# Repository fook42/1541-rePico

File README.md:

# 1541-rePico
replacement of analog-part of Commodore 1541-Floppy devices based on Pi-Pico(2)

## preface/credits ##
this project was derived from the original 1541-rebuild from Thorsten Kattanek (https://github.com/ThKattanek/1541-rebuild) !
parts of his code were taken from there and adopted for Raspberry Pico and modified to handle disk images differently. Thanks!

the C64/C16 selector-programm was developed and implemented by [PeiselUlli](https://github.com/peiselulli69) !

thanks to [BensonRSI](https://github.com/BensonRSI) for adding debugging documentation, dev-containers and github-magic !

## Features ##

latest version:
- software: 1.7.3
- hardware: 1.7.0

### Hardware ###

single board, size 59mm x 60 mm

- Raspberry Pico2 socket/solder-pads
- VIA 40pin socket
- levelshifter (BSS138 & 74LVC4245) for stable signals
- connectors for
  - I2C Display
  - SPI SD-Card adapter
  - Rotary-Encoder + Switch (KY-040 compatible)
  - Write-Protect-Signal
  - passive Buzzer

one size fits for all 1541 models.

## how to build ##

-> [interactive BOM](/hardware/bom/ibom.html)

-> [step-by-step guide](/doc/HWSetup.md)

### Software ###

#### Pico2 Firmware ####

- mounting of D64 & G64 & PRG Files
- 35 & 42 track image files supported
- read and write access for both D64 & G64
- sd-card hotswap feature (refresh of directory content)

#### C64/C16/VC20 Image Selector ####

- browsing through sd-card content via "virtual disk-image"
  - subdirectory support
  - 4 way scrolling
  - usage of joystick for browsing possible
- highlighting and selecting of different file-types (D64,G64,PRG,Folder)
- shows TXT files onscreen
- simple mounting and also fastloading of selected entry
- supports C64-PAL, C64-NTSC, VC20 and C16 computers

## how to build ##

### prepare tools (linux) ###

```
sudo apt install cmake libusb-1.0-0-dev build-essential pkg-config python3 xxd gcc-arm-none-eabi libnewlib-arm-none-eabi libstdc++-arm-none-eabi-newlib acme
```

### pico-sdk ###

from : <https://github.com/raspberrypi/pico-sdk>

- clone this repo
- create a environment variable called "PICO_SDK_PATH" which points to this repo
- place a "export PICO_SDK_PATH= <path to your pico-sdk>" at the end of your .profile script
- then cd into this repo-folder and initialize the mbedtls submodule (picotool mentiones this)

all in one:
```
git clone https://github.com/raspberrypi/pico-sdk.git
export PICO_SDK_PATH=$(pwd)/pico-sdk
echo "export PICO_SDK_PATH=$PICO_SDK_PATH" >> ~/.profile"
cd pico-sdk
git submodule update --init lib/mbedtls
```

### picotool ###

from : <https://github.com/raspberrypi/picotool>

- clone this repo
- install the picotool as described in README.md and BUILDING.md file there

```
git clone https://github.com/raspberrypi/picotool.git
```

### build steps ###

make sure submodules are initialized and up-to-date (like NoOS-Fat-lib)

```
git submodule update --init
git pull --recurse-submodules
```

prepare build-folder / configure Ninja for build the cmake project

```
cd firmware
mkdir build
cd build
cmake .. -D BUILD_MENUPRG=OFF -D COMPRESS_MENUPRG=ON -D PCB_VERSION=17
```

optional cmake variables are:

| Variable | Values | Description |
| :--- | :---: | :--- |
| BUILD_MENUPRG | ON*/OFF | let ACME compile the provided menu.asm-code. Otherwise the shipped, precompiled "menu.prg" will be used. |
| BUILD_SELECTORPRG | ON*/OFF | let PETCAT convert the boot-selector basic code to PRG. Otherwise the shipped, precompiled "selector.prg" will be used. |
| COMPRESS_MENUPRG | ON*/OFF | uses dali binary compression to generate a smaller menu-prg object |
| PCB_VERSION | 0..17* | defines which PCB version is used -> enables specific code features according to pcb-layout (like sound output) |

(* is default)

now trigger a build

```
make -j
```

## howto flash ##

connect your pico2 via USB cable and use picotool to flash the firmware

```
picotool load -t uf2 1541-rePico.uf2 -x -f
```

## debugging with OpenOCD ##

### prerequisites ###

- **CMSIS-DAP Compatible Debugger** (e.g., Raspberry Pi Debug Probe, STLink, or SEGGER J-Link) 
get binaries for a pico here : https://github.com/raspberrypi/debugprobe
- **OpenOCD** installed ( built in devcontainer or  with "build_openocd.sh")
- **gdb-multiarch** for GDB debugging ( preinstalled in devcontainer )

### setup ###

1. Connect your debugger to the Pico using the SWD pins:
   - SWCLK → GPIO 24 (or pin 20)
   - SWDIO → GPIO 25 (or pin 21)
   - GND → GND

2. Ensure the debugger is connected via USB to your development machine

### starting OpenOCD ###

Start OpenOCD in a terminal:

```
openocd -f interface/cmsis-dap.cfg -f target/rp2350.cfg
```

OpenOCD will listen on port 3333 for GDB connections.

### debugging in VS Code ###

VS Code launch configurations are available:

**Pico Debug (Cortex-Debug)** - Integrated debugging with OpenOCD

#### using Cortex-Debug (recommended) ####

Press `F5` or select "Pico Debug (Cortex-Debug)" from the Run menu. This will:
- Start OpenOCD automatically
- Load your firmware
- Break at `main()`
- Allow step debugging, breakpoints, and variable inspection

#### using external OpenOCD ####

1. Start OpenOCD in a terminal (see above)
2. Select "Pico Debug (Cortex-Debug with external OpenOCD)" from Run menu
3. VS Code will connect to the running OpenOCD instance

### useful GDB commands ###

When debugging, common GDB commands include:

```
continue         # Resume execution
step             # Step into function
next             # Step over function
break <func>     # Set breakpoint at function
break <file>:<line>  # Set breakpoint at file:line
print <var>      # Print variable value
display <var>    # Show variable on each step
backtrace        # Show call stack
```

### troubleshooting ###

**"Device not found"**: 
- Check CMSIS-DAP debugger is connected
- Verify SWD pin connections
- Try `openocd -d` for debug output
- Connect the USB for the targetdevice, then the USB for debugprobe
( to keep correct order of /dev/ttyACMx )

**GDB connection failed**: 
- Ensure OpenOCD is running on port 3333
- Check firewall settings

# documentation #

## project documentation ##

t.b.d.

## supported disk formats ##

currently [D64](/doc/D64.TXT) and [G64](/doc/G64.TXT) are supported as for reading and writing.  
as bonus, **PRG** files can be loaded by an on-the-fly routine that creates a valid D64 image out of it.

additionaly a small tool [conv_x64](/tools) is provided that allows easy conversion from one to the other on you linux-pc.

## Pictures ##

impressions of current setup and PCB can be found [here](/doc/pictures).

## Links ##

- great collection of basics about disk-image-formats can be found here:  
<https://ist.uwaterloo.ca/~schepers/formats.html>

- forum64 project discussion thread (base of 1541-rebuild and 1541-rePico)  
<https://www.forum64.de/index.php?thread/59884-laufwerk-der-1541-emulieren>

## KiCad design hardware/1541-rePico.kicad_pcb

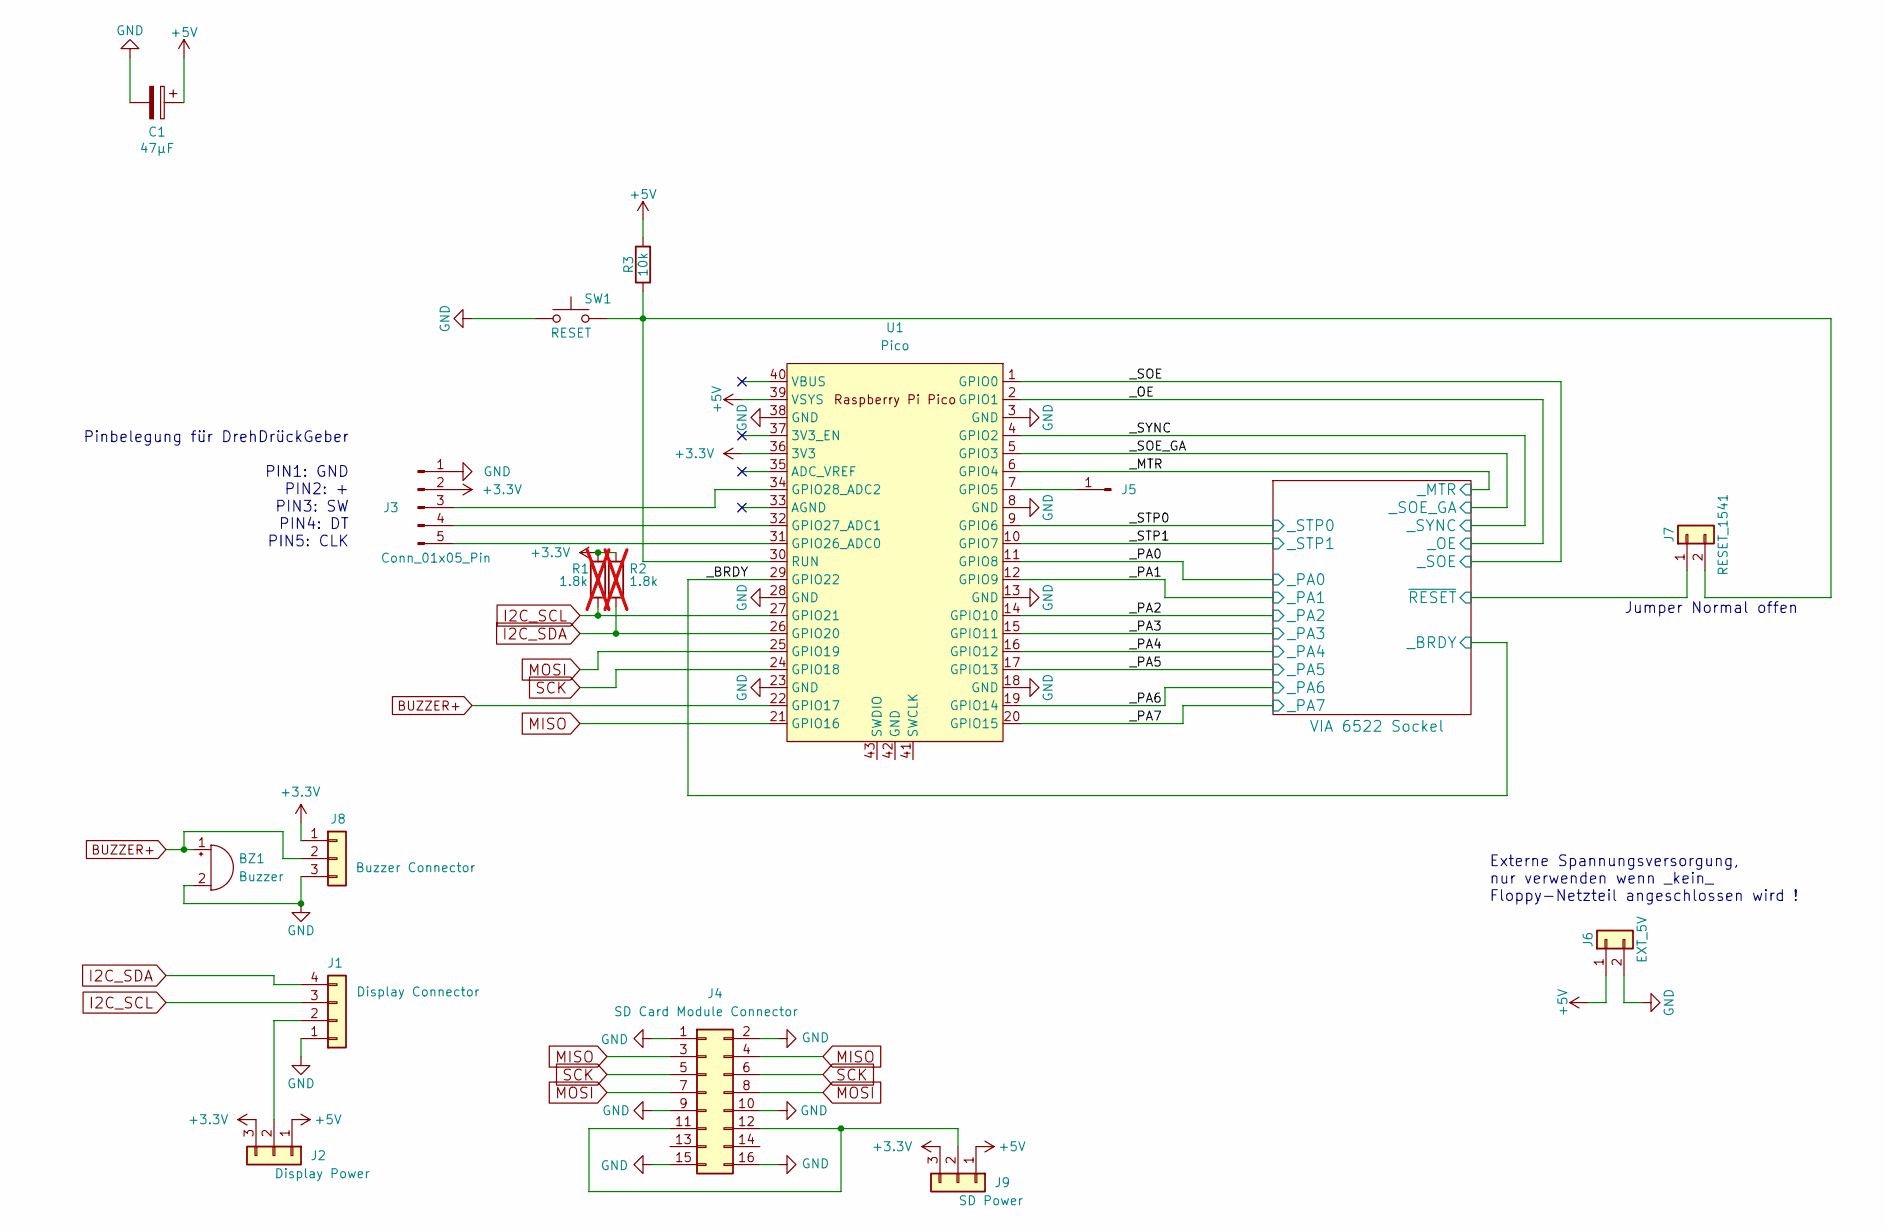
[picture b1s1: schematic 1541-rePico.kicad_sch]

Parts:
BZ1: Buzzer; MagneticBuzzer_StarMicronics_QMX
C1: 47µF; CP_Radial_D5.0mm_P2.50mm
J1: Display Connector; PinSocket_1x04_P2.54mm_Vertical
J2: Display Power; PinHeader_1x03_P2.54mm_Vertical
J3: Conn_01x05_Pin; PinHeader_1x05_P2.54mm_Vertical
J4: SD Card Module Connector; PinSocket_2x08_P2.54mm_Vertical
J5: Conn_01x01_Pin; PinHeader_1x01_P2.54mm_Vertical
J6: EXT_5V; PinHeader_1x02_P2.54mm_Vertical
J7: RESET_1541; PinHeader_1x02_P2.54mm_Vertical
J8: Buzzer Connector; PinHeader_1x03_P2.54mm_Vertical
J9: SD Power; PinHeader_1x03_P2.54mm_Vertical
R1, R2: 1.8k; R_0805_2012Metric; not fitted
R3: 10k; R_Axial_DIN0207_L6.3mm_D2.5mm_P10.16mm_Horizontal
SW1: RESET; SW_PUSH_6mm_H5mm
U1: Pico; RPi_Pico_SMD_TH

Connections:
+3.3V: J2.3, J3.2, J8.1, J9.3, R1.1, R2.1, U1.36 (3V3); also elsewhere on the board
+5V: C1.1, J2.1, J6.1, J9.1, R3.2, U1.39 (VSYS); also elsewhere on the board
/VIA 6522 Sockel/~RESET: J7.1; also elsewhere on the board
/_BRDY: U1.29 (GPIO22); also elsewhere on the board
/_MTR: U1.6 (GPIO4); also elsewhere on the board
/_OE: U1.2 (GPIO1); also elsewhere on the board
/_PA0: U1.11 (GPIO8); also elsewhere on the board
/_PA1: U1.12 (GPIO9); also elsewhere on the board
/_PA2: U1.14 (GPIO10); also elsewhere on the board
/_PA3: U1.15 (GPIO11); also elsewhere on the board
/_PA4: U1.16 (GPIO12); also elsewhere on the board
/_PA5: U1.17 (GPIO13); also elsewhere on the board
/_PA6: U1.19 (GPIO14); also elsewhere on the board
/_PA7: U1.20 (GPIO15); also elsewhere on the board
/_SOE: U1.1 (GPIO0); also elsewhere on the board
/_SOE_GA: U1.5 (GPIO3); also elsewhere on the board
/_STP0: U1.9 (GPIO6); also elsewhere on the board
/_STP1: U1.10 (GPIO7); also elsewhere on the board
/_SYNC: U1.4 (GPIO2); also elsewhere on the board
BUZZER+: BZ1.1 (+), J8.2, U1.22 (GPIO17)
GND: BZ1.2 (-), C1.2, J1.1, J3.1, J4.1, J4.2, J4.9, J4.10, J4.15, J4.16, J6.2, J8.3, SW1.1, U1.3 (GND), U1.8 (GND), U1.13 (GND), U1.18 (GND), U1.23 (GND), U1.28 (GND), U1.38 (GND); also elsewhere on the board
I2C_SCL: J1.3, R1.2, U1.27 (GPIO21)
I2C_SDA: J1.4, R2.2, U1.26 (GPIO20)
MISO: J4.3, J4.4, U1.21 (GPIO16)
MOSI: J4.7, J4.8, U1.25 (GPIO19)
unnamed: J1.2, J2.2
unnamed: J3.3, U1.34 (GPIO28_ADC2)
unnamed: J3.4, U1.32 (GPIO27_ADC1)
unnamed: J3.5, U1.31 (GPIO26_ADC0)
unnamed: J4.11, J4.12, J9.2
unnamed: J5.1, U1.7 (GPIO5)
unnamed: J7.2, R3.1, SW1.2, U1.30 (RUN)
SCK: J4.5, J4.6, U1.24 (GPIO18)

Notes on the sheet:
Jumper Normal offen
Externe Spannungsversorgung, nur verwenden wenn _kein_ Floppy-Netzteil angeschlossen wird !
Pinbelegung für DrehDrückGeber PIN1: GND PIN2: + PIN3: SW PIN4: DT PIN5: CLK

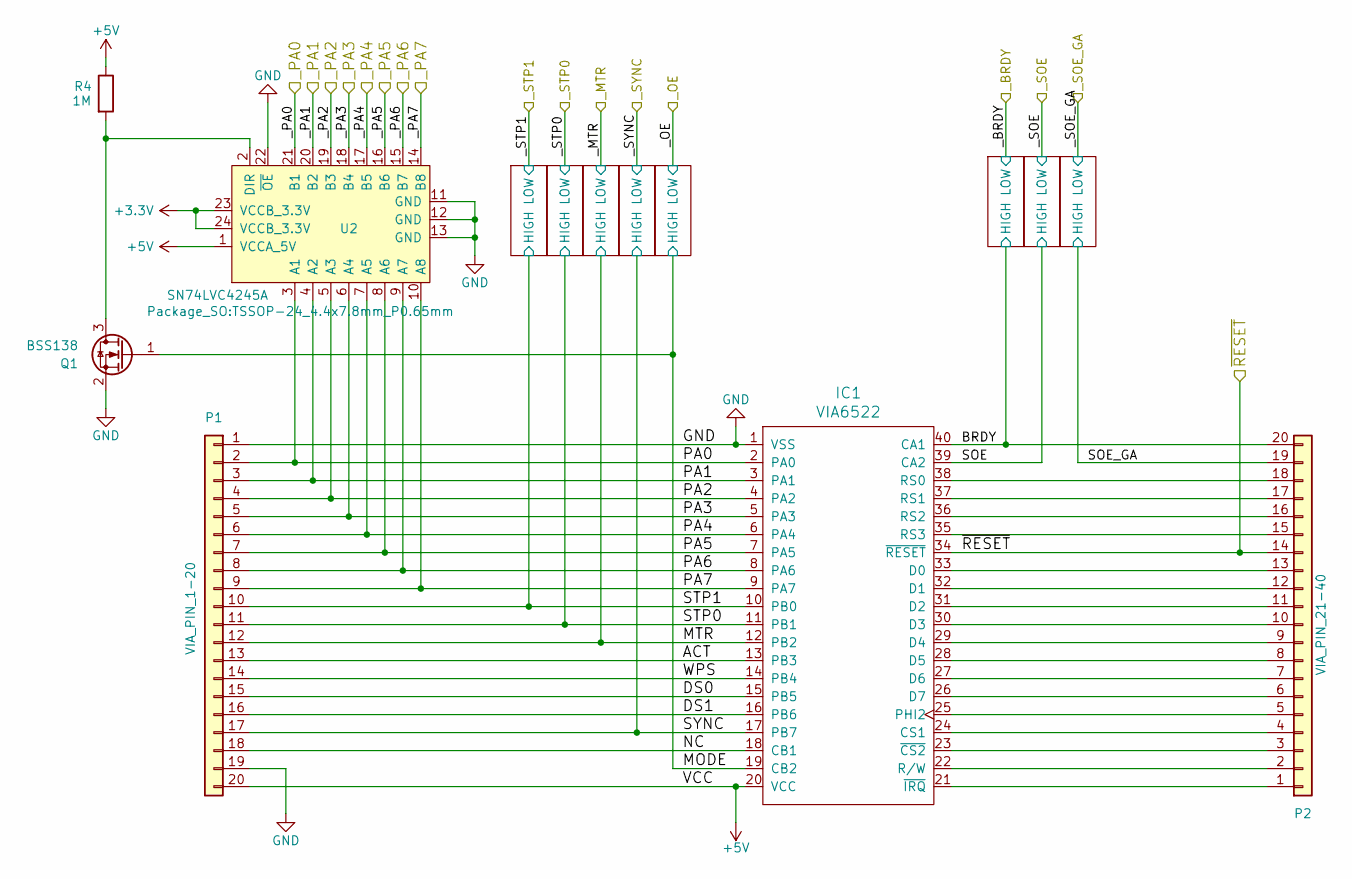
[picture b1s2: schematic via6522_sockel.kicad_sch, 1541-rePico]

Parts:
IC1: VIA6522; DIP-40_W15.24mm_Socket_LongPads
P1: VIA_PIN_1-20; PinHeader_1x20_P2.54mm_Vertical
P2: VIA_PIN_21-40; PinHeader_1x20_P2.54mm_Vertical
Q1: BSS138; SOT-23
R4: 1M; R_0603_1608Metric
U2: SN74LVC4245A; TSSOP-24_4.4x7.8mm_P0.65mm

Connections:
+3.3V: U2.23 (VCCB_3.3V), U2.24 (VCCB_3.3V); also elsewhere on the board
+5V: IC1.20 (VCC), P1.20, R4.1, U2.1 (VCCA_5V); also elsewhere on the board
/VIA 6522 Sockel/ACT: IC1.13 (PB3), P1.13
/VIA 6522 Sockel/BRDY: IC1.40 (CA1), P2.20; also elsewhere on the board
/VIA 6522 Sockel/DS0: IC1.15 (PB5), P1.15
/VIA 6522 Sockel/DS1: IC1.16 (PB6), P1.16
/VIA 6522 Sockel/MODE: IC1.19 (CB2), Q1.1 (G); also elsewhere on the board
/VIA 6522 Sockel/MTR: IC1.12 (PB2), P1.12; also elsewhere on the board
/VIA 6522 Sockel/NC: IC1.18 (CB1), P1.18
/VIA 6522 Sockel/PA0: IC1.2 (PA0), P1.2, U2.3 (A1)
/VIA 6522 Sockel/PA1: IC1.3 (PA1), P1.3, U2.4 (A2)
/VIA 6522 Sockel/PA2: IC1.4 (PA2), P1.4, U2.5 (A3)
/VIA 6522 Sockel/PA3: IC1.5 (PA3), P1.5, U2.6 (A4)
/VIA 6522 Sockel/PA4: IC1.6 (PA4), P1.6, U2.7 (A5)
/VIA 6522 Sockel/PA5: IC1.7 (PA5), P1.7, U2.8 (A6)
/VIA 6522 Sockel/PA6: IC1.8 (PA6), P1.8, U2.9 (A7)
/VIA 6522 Sockel/PA7: IC1.9 (PA7), P1.9, U2.10 (A8)
/VIA 6522 Sockel/SOE: IC1.39 (CA2); also elsewhere on the board
/VIA 6522 Sockel/SOE_GA: P2.19; also elsewhere on the board
/VIA 6522 Sockel/STP0: IC1.11 (PB1), P1.11; also elsewhere on the board
/VIA 6522 Sockel/STP1: IC1.10 (PB0), P1.10; also elsewhere on the board
/VIA 6522 Sockel/SYNC: IC1.17 (PB7), P1.17; also elsewhere on the board
/VIA 6522 Sockel/WPS: IC1.14 (PB4), P1.14
/VIA 6522 Sockel/~RESET: IC1.34 (~RESET), P2.14; also elsewhere on the board
/_PA0: U2.21 (B1); also elsewhere on the board
/_PA1: U2.20 (B2); also elsewhere on the board
/_PA2: U2.19 (B3); also elsewhere on the board
/_PA3: U2.18 (B4); also elsewhere on the board
/_PA4: U2.17 (B5); also elsewhere on the board
/_PA5: U2.16 (B6); also elsewhere on the board
/_PA6: U2.15 (B7); also elsewhere on the board
/_PA7: U2.14 (B8); also elsewhere on the board
GND: IC1.1 (VSS), P1.1, P1.19, Q1.2 (S), U2.11 (GND), U2.12 (GND), U2.13 (GND), U2.22 (~OE); also elsewhere on the board
unnamed: IC1.24 (CS1), P2.4
unnamed: IC1.33 (D0), P2.13
unnamed: IC1.32 (D1), P2.12
unnamed: IC1.31 (D2), P2.11
unnamed: IC1.30 (D3), P2.10
unnamed: IC1.29 (D4), P2.9
unnamed: IC1.28 (D5), P2.8
unnamed: IC1.27 (D6), P2.7
unnamed: IC1.26 (D7), P2.6
unnamed: IC1.25 (PHI2), P2.5
unnamed: IC1.38 (RS0), P2.18
unnamed: IC1.37 (RS1), P2.17
unnamed: IC1.36 (RS2), P2.16
unnamed: IC1.35 (RS3), P2.15
unnamed: IC1.22 (R/W), P2.2
unnamed: IC1.23 (~CS2), P2.3
unnamed: IC1.21 (~IRQ), P2.1
unnamed: Q1.3 (D), R4.2, U2.2 (DIR)

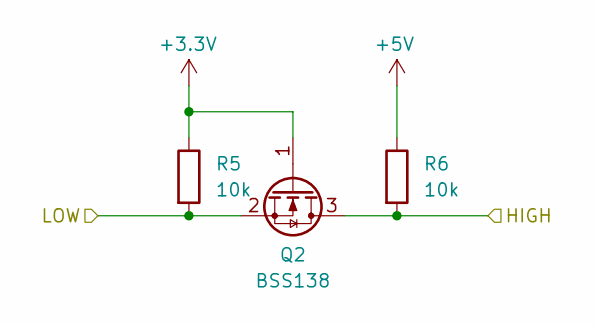
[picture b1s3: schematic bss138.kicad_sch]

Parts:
Q2: BSS138; SOT-23
R5, R6: 10k; R_0603_1608Metric

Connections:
+3.3V: Q2.1 (G), R5.1; also elsewhere on the board
+5V: R6.1; also elsewhere on the board
/VIA 6522 Sockel/STP1: Q2.3 (D), R6.2; also elsewhere on the board
/_STP1: Q2.2 (S), R5.2; also elsewhere on the board

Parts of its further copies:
Q3, Q4, Q5, Q6, Q7, Q8, Q9: BSS138; SOT-23
R7, R8, R9, R10, R11, R12, R13, R14, R15, R16, R17, R18, R19, R20: 10k; R_0603_1608Metric

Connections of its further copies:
+3.3V: Q3.1 (G), Q4.1 (G), Q5.1 (G), Q6.1 (G), Q7.1 (G), Q8.1 (G), Q9.1 (G), R7.1, R9.1, R11.1, R13.1, R15.1, R17.1, R19.1; also elsewhere on the board
+5V: R8.1, R10.1, R12.1, R14.1, R16.1, R18.1, R20.1; also elsewhere on the board
/VIA 6522 Sockel/BRDY: Q7.3 (D), R16.2; also elsewhere on the board
/VIA 6522 Sockel/MODE: Q6.3 (D), R14.2; also elsewhere on the board
/VIA 6522 Sockel/MTR: Q4.3 (D), R10.2; also elsewhere on the board
/VIA 6522 Sockel/SOE: Q8.3 (D), R18.2; also elsewhere on the board
/VIA 6522 Sockel/SOE_GA: Q9.3 (D), R20.2; also elsewhere on the board
/VIA 6522 Sockel/STP0: Q3.3 (D), R8.2; also elsewhere on the board
/VIA 6522 Sockel/SYNC: Q5.3 (D), R12.2; also elsewhere on the board
/_BRDY: Q7.2 (S), R15.2; also elsewhere on the board
/_MTR: Q4.2 (S), R9.2; also elsewhere on the board
/_OE: Q6.2 (S), R13.2; also elsewhere on the board
/_SOE: Q8.2 (S), R17.2; also elsewhere on the board
/_SOE_GA: Q9.2 (S), R19.2; also elsewhere on the board
/_STP0: Q3.2 (S), R7.2; also elsewhere on the board
/_SYNC: Q5.2 (S), R11.2; also elsewhere on the board

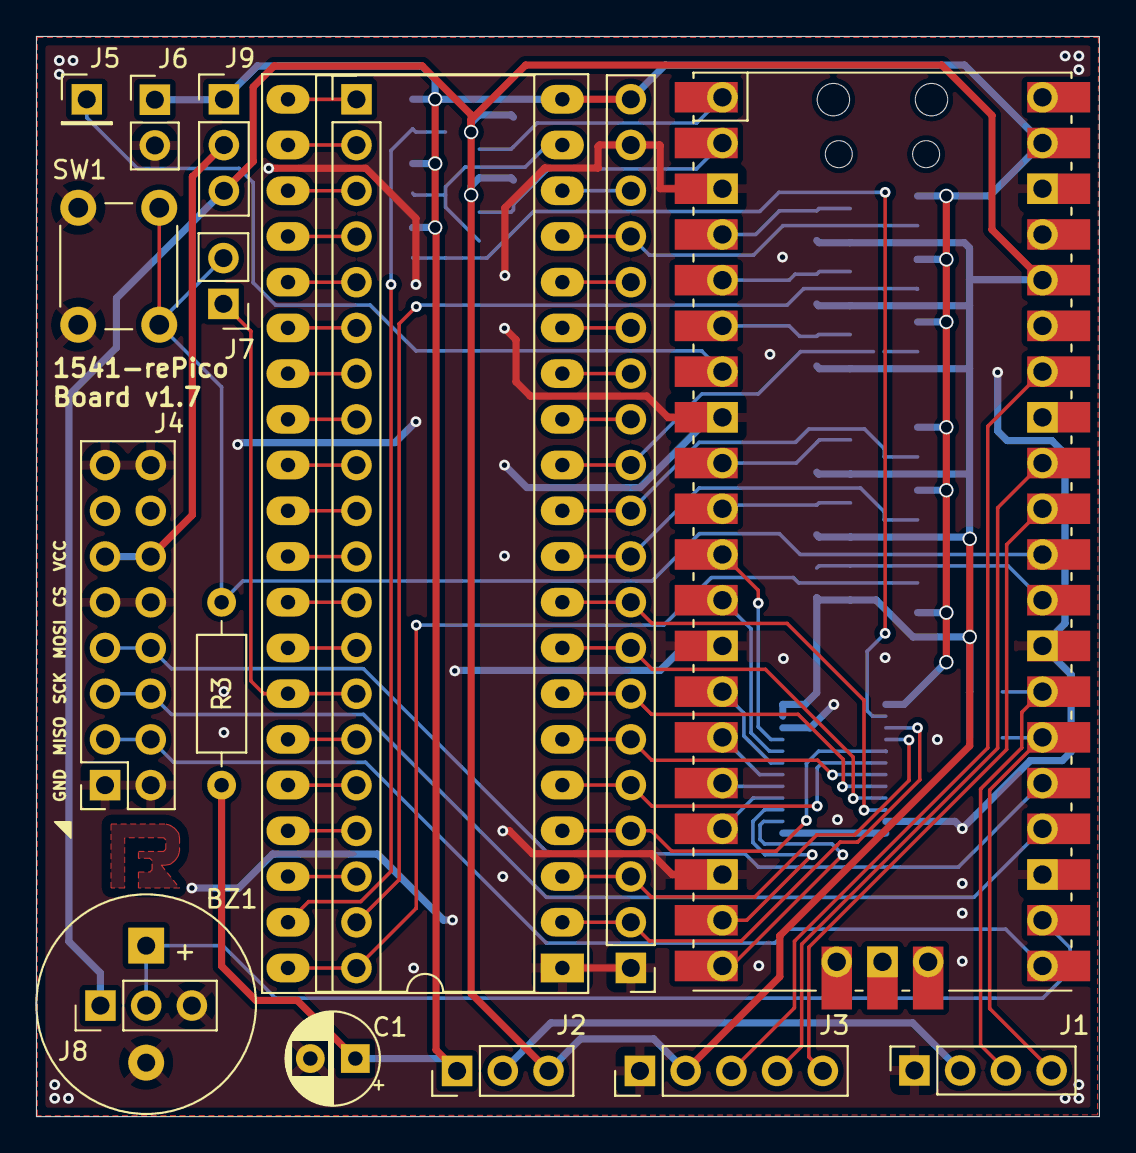
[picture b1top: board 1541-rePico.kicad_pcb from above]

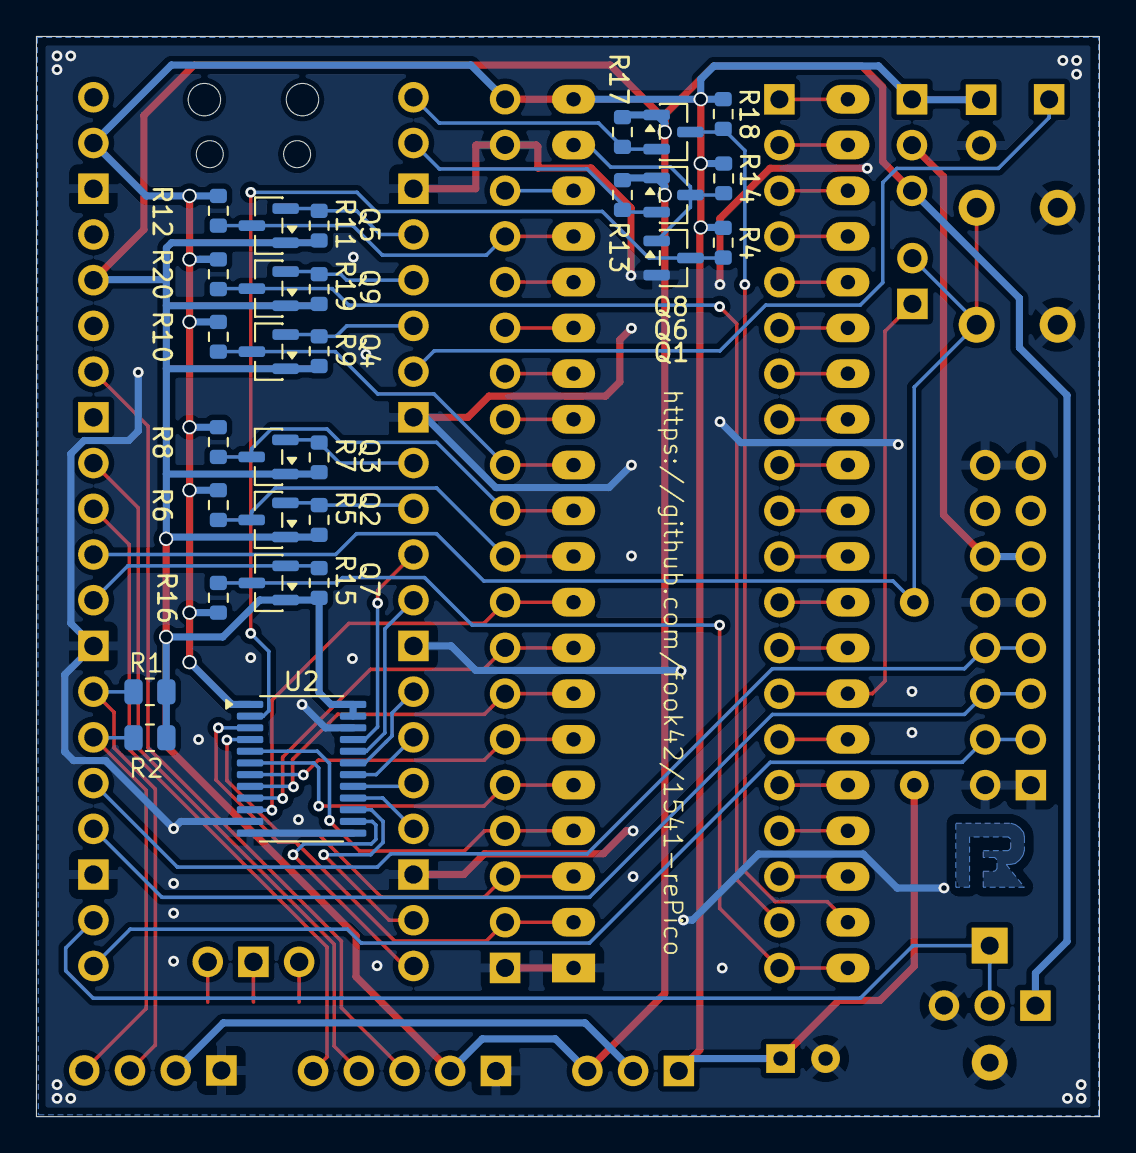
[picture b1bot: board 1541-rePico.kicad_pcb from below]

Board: 2 copper layers, 59.1 x 60.0 mm, 46 parts (29 on the bottom side), 72 nets.

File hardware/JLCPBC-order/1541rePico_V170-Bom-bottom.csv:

"Comment","Designator","Footprint","JLCPCB Part #"
"1M","R4","Resistor_SMD:R_0603_1608Metric","C22935"
"SN74LVC4245A","U2","Package_SO:TSSOP-24_4.4x7.8mm_P0.65mm","C7859"
"BSS138","Q1,Q2,Q3,Q4,Q5,Q6,Q7,Q8,Q9","Package_TO_SOT_SMD:SOT-23","C7420339"
"10k","R5,R6,R7,R8,R9,R10,R11,R12,R13,R14,R15,R16,R17,R18,R19,R20","Resistor_SMD:R_0603_1608Metric","C25804"

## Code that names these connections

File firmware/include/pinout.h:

/**********************************
 * header - pinout assignment for Pico2 to baseboard
 *
 * Author: F00K42
 * Last change: 2026/07/24
***********************************/

#include "hardware/spi.h"

// Via connection
#define GPIO_SOE    0
#define GPIO_OE     1
#define GPIO_SYNC   2
#define GPIO_SOE_GA 3
#define GPIO_MTR    4
#define GPIO_WPS    5
#define GPIO_STP0   6
#define GPIO_STP1   7

#define GPIO_PAPORT 8  //defines the first bit of 8
#define PAPORT_MASK (uint32_t)(0xFF<<GPIO_PAPORT)
/*
#define GPIO_PA0    8
#define GPIO_PA1    9
#define GPIO_PA2    10
#define GPIO_PA3    11
#define GPIO_PA4    12
#define GPIO_PA5    13
#define GPIO_PA6    14
#define GPIO_PA7    15
*/

// SPI defines
#define SPI_PORT    spi0
#define SPI_MISO    16
#define SPI_SCK     18
#define SPI_MOSI    19

// I2C defines
#define I2C_PORT    i2c0
#define I2C_SDA     20
#define I2C_SCL     21

// 3 für den Drück-Dreh-Schalter
#define GPIO_BT1    27
#define GPIO_BT2    26
#define GPIO_BT3    28

#define GPIO_BRDY   22

#define NOT_CONNECTED (-1)


#if PCB_VERSION>=17
#define GPIO_SND    17
#define SPI_CS      NOT_CONNECTED
#else
#define GPIO_SND    NOT_CONNECTED
#define SPI_CS      17
#endif

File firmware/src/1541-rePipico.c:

#include <stdio.h>
#include "pico/stdlib.h"
// #include "hardware/spi.h"
#include "hardware/i2c.h"
// #include "hardware/dma.h"
// #include "hardware/pio.h"
// #include "hardware/interp.h"
#include "hardware/timer.h"
#include "hardware/clocks.h"

#include "pinout.h"

#define _EXTERN_

#include "display.h"
#include "lcd.h"
#include "oled.h"
#include "i2c.h"
#include "gcr.h"
#include "menu.h"

#include "hw_config.h"
#include "f_util.h"
#include "ff.h"

uint8_t stepper_signal_puffer[0x80]; // Ringpuffer für Stepper Signale (128 Bytes)
volatile uint8_t stepper_signal_r_pos = 0;
volatile uint8_t stepper_signal_w_pos = 0;
volatile uint8_t stepper_signal_time = 0;
volatile uint8_t stepper_signal = 0;

// -- MENU preparation --
MENU_STRUCT main_menu;
MENU_STRUCT image_menu;
MENU_STRUCT settings_menu;
MENU_STRUCT info_menu;

enum  MENU_IDS{M_BACK, M_IMAGE, M_SETTINGS, M_INFO, \
               M_BACK_IMAGE, M_INSERT_IMAGE, M_UNMOUNT_IMAGE, M_WP_IMAGE, M_NEW_IMAGE, M_SAVE_IMAGE, \
               M_BACK_SETTINGS, M_PIN_PB2, M_PIN_PB3, M_SAVE_EEPROM, M_RESTART, \
               M_BACK_INFO, M_VERSION_INFO, M_SDCARD_INFO};

/// Hauptmenü
MENU_ENTRY main_menu_entrys[] = {{"Disk Menu", M_IMAGE,ENTRY_MENU,   0,&image_menu},
                                {"Settings",  M_SETTINGS,ENTRY_MENU,0,&settings_menu},
                                {"Info",      M_INFO,ENTRY_MENU,    0,&info_menu}};
/// Image Menü
MENU_ENTRY image_menu_entrys[] = {{"Insert Image", M_INSERT_IMAGE},
                                {"Unmount Image",M_UNMOUNT_IMAGE},
                                {"WriteProt.",   M_WP_IMAGE,ENTRY_ONOFF,1},
                                {"New Image",    M_NEW_IMAGE},
                                {"Save Image",   M_SAVE_IMAGE}};
/// Setting Menü
MENU_ENTRY settings_menu_entrys[] = {{"Pin PB2",M_PIN_PB2, ENTRY_ONOFF, 0},
                                    {"Pin PB3",M_PIN_PB3, ENTRY_ONOFF, 0},
                                    {"Restart",M_RESTART}};
/// Info Menü
MENU_ENTRY info_menu_entrys[] = {{"Version",     M_VERSION_INFO},
                                {"SD Card Info",M_SDCARD_INFO}};
// -----------

void gpio_callback(uint gpio, uint32_t events)
{
    // general gpio-ISR .. triggered for STP0 or STP1 change.. no need to detect the cause
    stepper_signal_puffer[stepper_signal_w_pos & 0x7F] = ((bool_to_bit(gpio_get(GPIO_STP0))) | (bool_to_bit(gpio_get(GPIO_STP1))<<1));
    stepper_signal_w_pos++;
}


int main()
{
    stdio_init_all();

    // set interrupt on pin-change for STP0 and STP1 ...
    gpio_init(GPIO_STP0);
    gpio_init(GPIO_STP1);
    gpio_set_dir(GPIO_STP0, GPIO_IN);
    gpio_set_dir(GPIO_STP1, GPIO_IN);
    gpio_set_irq_enabled_with_callback(GPIO_STP0, GPIO_IRQ_EDGE_RISE | GPIO_IRQ_EDGE_FALL, true, &gpio_callback);
    gpio_set_irq_enabled(GPIO_STP1, GPIO_IRQ_EDGE_RISE | GPIO_IRQ_EDGE_FALL, true);

    // // SPI initialisation. This example will use SPI at 1MHz.
    // spi_init(SPI_PORT, 1000*1000);
    // gpio_set_function(SPI_MISO, GPIO_FUNC_SPI);
    // gpio_set_function(SPI_CS,   GPIO_FUNC_SIO);
    // gpio_set_function(SPI_SCK,  GPIO_FUNC_SPI);
    // gpio_set_function(SPI_MOSI, GPIO_FUNC_SPI);
    

    // // gpio_put_masked(0xFF<<GPIO_PAPORT,value<<GPIO_PAPORT);

    // // Chip select is active-low, so we'll initialise it to a driven-high state
    // gpio_set_dir(SPI_CS, GPIO_OUT);
    // gpio_put(SPI_CS, 1);
    // // For more examples of SPI use see https://github.com/raspberrypi/pico-examples/tree/master/spi

    if (display_init())
    {
        display_clear();
        display_home();
    }

    FATFS fs;
    FRESULT fr = f_mount(&fs, "", 1);
    uint8_t retry_count = 3;

    while ((FR_OK != fr) && (retry_count > 0)) {
        display_setcursor(0, 0);
        display_string("f_mount error:");
        display_data(fr+'0');
        display_setcursor(0, 1);
        display_print(FRESULT_str(fr),0,16);
        display_setcursor(0, 2);
        display_print(FRESULT_str(fr),16,16);
        display_setcursor(0, 3);
        display_string("retrying ...");
        display_data(retry_count+'0');
        retry_count--;
        sleep_ms(2000);
        FRESULT fr = f_mount(&fs, "", 1);
        display_clear();
    }

    display_setcursor(0, 0);
    display_string("f_mount okay");

    sleep_ms(3000);

    display_clear();
    display_home();

    DIR dir_object;
    FILINFO dir_entry;

    uint8_t dsp_zeile = 0;

    fr = f_findfirst(&dir_object, &dir_entry, "", "*");

    while ((fr == FR_OK) && (dir_entry.fname[0]!=0))
    {
        display_setcursor(0, dsp_zeile);
        display_data(display_cursor_char);
        display_print(dir_entry.fname, 0, 12);
        dsp_zeile = (dsp_zeile+1)%4;
        if (0 == dsp_zeile)
        {
            sleep_ms(2000);
            display_clear();
        }
        fr = f_findnext(&dir_object, &dir_entry);
    }
    display_setcursor(0, dsp_zeile);
    display_string("--END--");

    sleep_ms(5000);

    // setup menus
    menu_init(&main_menu,     main_menu_entrys,     count_of(main_menu_entrys),     LCD_COLS, LCD_ROWS);
    menu_init(&image_menu,    image_menu_entrys,    count_of(image_menu_entrys),    LCD_COLS, LCD_ROWS);
    menu_init(&settings_menu, settings_menu_entrys, count_of(settings_menu_entrys), LCD_COLS, LCD_ROWS);
    menu_init(&info_menu,     info_menu_entrys,     count_of(info_menu_entrys),     LCD_COLS, LCD_ROWS);

    menu_set_root(&main_menu);
    // ----

    // uint8_t stepper;
    // stepper_signal_puffer[0]=212; // fake data 11010100
    // stepper_signal_w_pos++;



    while (true) {
        menu_refresh();

        //        printf("Hello, world!\n");
        // if (stepper_signal_r_pos != stepper_signal_w_pos)
        // {
        //     display_clear();
        //     display_setcursor(0, 0);
        //     stepper = stepper_signal_puffer[stepper_signal_r_pos & 0x7F] | stepper_signal_puffer[(stepper_signal_r_pos-1) & 0x7F]<<2;
        //     stepper_signal_r_pos++;

        //     for (int i=7; i>=0; --i)
        //     {
        //         display_data((stepper&(1<<i))?'1':'0');
        //     }
        // }
        sleep_ms(1000);
    }
}

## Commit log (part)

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2025-10-27 first commit with basics
    folder-structure established
    pcb-layout added
    firmware based on blink-example
    verified i2c-display routines
    added no-OS-FatFS lib as submodule
2025-10-31 updated PCB layout
2025-10-31 first sdcard-access
2025-10-31 remove pio-blink-code
2025-12-18 refactored some files/code
2025-12-18 added schematic as pdf
2025-12-29 enable filebrowser functions
2026-01-02 added D64 read+GCR convert routine
2026-01-05 added G64 image read
2026-01-06 more functions from 1541-rebuild adopted
2026-01-07 added more 1541-gpios and timer-ISR
2026-01-13 updated schematics&pcb - version 1.1
2026-01-13 fixed input and code cleanup
    removed pio-code - access to variables blocked the system
    fixed interrupt routines for stepper and track handling
2026-01-16 code cleanup and tuning
    removed comments
    change datastructures for jumptable and speedzones
    g64 read improved
2026-02-07 major testing
    - removed sprintf, replaced with dec2out (IT2)
    - tracks from 0 to 41 (no dead buffers)
    - stepper reworked (no direct steps, but after 193*byte_ready)
2026-02-09 bigger mod
    - stepper wait done via alarm method
    - removed debug-output
    - change of input debouncing (not perfect)
2026-02-10 fixed disk-change
    cleanup of write-protection-signal
    renamed functions to "enable_.." and "disable.."
    for better readability
2026-02-11 fix WPS cross-driving
    connection between 1541-board and VIA cut off
    no cross driving of existing 74LS04 and Pico avoided
2026-02-11 updated kicad-data for PCB v1.2
2026-02-11 input irq routine reworked
    removed "counter" value to detect rotary input
    simplyfied by KEY-values that are set
    debounce/blocking mechanism with alarm-timer
    fixes issue #3
2026-02-12 first attempt for better WPS handling
    a)disconnect WPS from Pico
    b)still connect 1541-mainboard WPS with VIA on 1541-rePico
    c)connect Pico-WPS output to input of 1541-mainboard
    input of photo-sensor (=1541-II -> CN4,pin3)
    d)invert Pico-output as 1541-board does the inversion again
2026-02-12 write-routines for g64 and d64
2026-02-14 add a conversion helper tool
2026-02-14 refactoring of code parts
    created global.c/.h to hold global variables and defines
    created rw_routines.c/.h for image-read and -write routines
    goal: cleaning out main.c/main.h files
2026-02-15 new PCB layout + BRDY fix
    changed rotary-encoder connector to default 5 pin
    flipped BRDY signal (GPIO28) with BT3 (GPIO22) to
    not violate 5V tollerance of GPIO28.
2026-02-15 added documents for new PCB1.3 pinout
2026-02-15 enabled image-write-routine
    SAVE_IMAGE will dump current gcr-data
    filename and type is fixed to
    1541-repico.g64 and G64 format
2026-02-15 block changes while writing image
2026-02-16 new PCB layout to support WPS external
    invert WPS signal to be used as input of photo-sensor
    circuit of 1541-main pcb.
    avoids the concurrent access of the WPS signal between
    GateArray and VIA - now this comes from 74LS04
2026-02-17 disk id reading, write prot from file
    reading DOS-disk id from D64 and G64
    used file-protection bits from SD-card FS to
    set write-protection status
2026-02-17 updated kicad-files for gerber creation
2026-03-14 SD card handling modified
    moved SD-card mounting to subroutine
    access on each "file-browser" activation
    added sd-card info display
2026-03-26 updated to version 1.4.0
    input-button handling improved: longpress for "back" function
    menu structure adopted: back entry added
    changed startup: sd-card mounting only when accessing images
    write-protect mode changed accordingly to PCB change (WPS jumper wire)
    added sd-card info-screen: partition infos .. but not much yet
    improved oled-output: brighter output on 128x64 oled (double scanline)
2026-03-28 new PCB version 1.5
    - added levelshifter ics txs0108epwr between pico and via pins
    - added pullup-resistors for I2C (populate if necessary)
    - aligned footprint of jumper-headers on 50mil grid
    - added version-text and URL on backside
2026-04-03 minor updates to pcb
2026-04-12 PCB version 1.6
    - use of SN74LVC4245A for levelshifting of PortB-Signals
    -> needed an inverted Mode/OE signal for DIR (done via BSS138)
    - use of BSS138 for shifting of basic signals (MTR, STP,...)
    - cut off "mode/OE" pin from Gatearray -> tied to GND to not let it drive PortB
    - rerouted the PCB again -> alignment of Pinheaders and vias
2026-04-13 updated PDFs for PCB v1.6
2026-05-02 added some docs, update Readme.md
2026-05-02 corrected doc-link
2026-05-03 added pictures of ready rePico
2026-05-03 update to README
2026-05-03 minor changes to README
2026-05-03 Docu branch (#15)
    * added some docs, update Readme.md
    * corrected doc-link
    * added pictures of ready rePico
    * update to README
2026-05-09 menu-image created
    on bootup/startup, an empty image is created in ram
    containing a bam+directory (load"$"+list will show)
    entries are filenames on SDcard - as PRG
    folders on the SDcard are marked "<" behind
2026-05-10 code cleanup for menu-image creation
    moved convert track routine to rw_routines - reuse possible
    empty image creation reduced
    bam creation enhanced with dostype setting
    directory creation optimized and enhanced to support ~128 entries
2026-05-10 fix to undo buffer changes when converting
2026-05-13 fixed submodule entry of noOS-FSLib
2026-05-14 creation of selector image
    data-file will be created from sdcard-filelist
    virtual image will be created with bam+dir+data-file
2026-05-14 fixed manual branch-mix
2026-05-16 included selector.prg to virtal menu-image
    added cmake-step to convert binary to headerfile for menu.prg
    added generic transfer function from binary to sector/tracks
    added directory-generation
2026-05-16 create selector-image on boot
2026-05-16 small change/fix to menu.prg
2026-05-16 included a Selector-View
    added menu-entries for Selector
    added new function to convert gcr-track to d64 buffer
    moved open-dir-entry routine to a separate function
    implemented readback from selector (directory-track/sector 2)
    triggering image-loading of selected image
2026-05-16 minor change to busy-anim
2026-05-17 updated README.md for tools
2026-05-17 small fix for case/variable problem
2026-05-19 added PRG handling stub
2026-05-19 PRG Loader-Image created
2026-05-21 update of menu.prg selector
    packed binary - shorter file-load
    enhanced by showing directory-name
    scrolling of long filenames
2026-05-21 reworked menu-image creation
    menu-datafile will now be created first in scratch area
    and then converted/placed into data-tracks - limit is 17 tracks now
    removed "animation" for selector .. now info-gui is shown
2026-05-22 added magic sleep after remote-image selection
2026-05-23 added better path handling
2026-05-23 first fix for subdirectories, chdir
2026-05-23 sub-sub folder handling fixed
2026-05-24 updated menu.prg
2026-05-24 subdirectory-handling,autostart,longpress diskchange
2026-05-24 added versioninfo to first select-level
2026-05-25 updated version-string
2026-05-25 updated README with new features
2026-05-25 Selector image (#16)
    * creation of selector image
    data-file will be created from sdcard-filelist
    virtual image will be created with bam+dir+data-file
    * fixed manual branch-mix
    * included selector.prg to virtal menu-image
    added cmake-step to convert binary to headerfile for menu.prg
2026-05-25 chore: rebase to lastest main
2026-05-25 chore: rebase to lastest main (#17)
2026-05-26 feat: gh_actions for build
2026-05-26 feat: gh_actions for build
    feat: gh_actions for build
    feat: gh_actions for build
    feat: gh_actions for build
    feat: gh_actions for build
    feat: gh_actions for build
    feat: gh_actions for build
2026-05-27 feat: added gh-action for code analysis
2026-05-27 feat: added gh-action for release
2026-05-27 chore: update to latest version from xxd
2026-05-27 chore: update to latest version from xxd (#20)
2026-06-04 added intro-prg from Benson
2026-06-04 intro update, including instructions
2026-06-04 corrections for code-checker findings
2026-06-09 added source of selector-menu
2026-06-10 added C64 fastload-bins for menu-prg
2026-06-11 added re-insert function
2026-06-12 added cmake build-step for menu.prg
2026-06-12 NO_CACHE not NOCACHE
2026-06-12 added compression for menu-prg with dali as option
2026-06-14 minor change selector-anim
2026-06-14 bugfix stepper_buffer overflow
2026-06-15 fixed code analysis findings
2026-06-15 added acme to devcontainer
2026-06-15 Revert "added acme to devcontainer"
    This reverts commit ee1474e4ce826ec64720ca40513ff8aec7a3695b.
2026-06-15 more fixes for code analysis
2026-06-20 added low-pass filter for stepper-signals (freespin-demo)
    stepper movement is now only possible if min. 5ms are between
    stepping changes. real hardware will not respond to this, but may make
    some noise (=sound)
    this enables the freespin-demo to be running well - only "real" head-movement
    will be simulated.
2026-06-20 Update code-analysis.yml
    added -I for include-headers
2026-06-20 global variable cleanup
2026-06-20 fixed copy-n-paste error
2026-06-21 code refactoring, small fix for PRG size value
    removed some unused variables
    changed code structure in rw-routines
    fixed prg-len calculation (size/254 instead of 253)
    bumped version to 1.6.2
2026-06-23 added dali as submodule
